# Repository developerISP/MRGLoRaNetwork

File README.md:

# Col Margherita LoRa Project (ROSY: Remote Observatory SYstem)
This is the repository for the school-work project between the Istitute of Polar Science ISP-CNR of Venice and the ITIS Max Planck of Villorba (TV)

# Who
The wonderful people involved in the ROSY project are all students, as they will never stop to learn! 

The young team in electronics, computer science, power management and telecommunications that built up the work is:
Nicolò Baseggio,
Davide Dal Bo,
Andrea De Marchi,
Michele Ferrarese,
Massimiliano Granziol,
Marco Martini,
Silvia Mondin,
Federico Peruzzo,
Roberto Pomiato,
Nicolò Rasera,
Nicola Voltarel

The group is trained and motivated by selfless and great teachers:
Alessandro Rocco Monteduro,
Monica Disarò,
Eugenio Rossi,
Giorgio Damian

The project is coordinated by enthusiastic researchers:
Federico Dallo,
Daniele Zannoni,
Fabrizio De Blasi,
Jacopo Gabrieli,
Carlo Barbante

# When
The project started in January 2020, continued throughout the tough Covid-19 pandemic thanks to the great motivation of the students and is on its way to be completed during the spring 2021. We were able to continue the development of hardware and software thanks to the distance learing (DAD) and tele-work. We have met at the ITIS Max Planck laboratories to build up the instrumentations and to perform several test, such as measuring the power comsumption and telecommunication capabilieties of the instruments. We were hosted at the Ca' Foscari University Campus in Via Torino and at the National Research Council (CNR) Col Margherita Observatory in the Belluno province.

# How

# Why

# Network
Files related to the acquisition, communication and ... are organized in the "network" directory. 

# Meteorology
Files for the analysis of meteorological variables are organized in the "meteorology" directory.
```
.
└── meteorology
    ├── data
    │   ├── MRG_2017_2018.csv
    │   └── P_Valles_2010_2020.csv
    ├── main.R
    └── outputs
        ├── MRGatmosphericpressuretypicalyear.csv
        ├── MRGatmosphericpressuretypicalyear.png
        ├── MRGrelativehumiditytypicalyear.csv
        ├── MRGrelativehumiditytypicalyear.png
        ├── MRGsolarradiationtypicalyear.csv
        ├── MRGsolarradiationtypicalyear.png
        ├── MRGtemperaturetypicalyear.csv
        ├── MRGtemperaturetypicalyear.png
        ├── MRGwinddirectiontypicalyear_autunno.png
        ├── MRGwinddirectiontypicalyear.csv
        ├── MRGwinddirectiontypicalyear_estate.png
        ├── MRGwinddirectiontypicalyear_inverno.png
        ├── MRGwinddirectiontypicalyear_primavera.png
        ├── MRGwindspeedtypicalyear.csv
        └── MRGwindspeedtypicalyear.png

3 directories, 18 files
```

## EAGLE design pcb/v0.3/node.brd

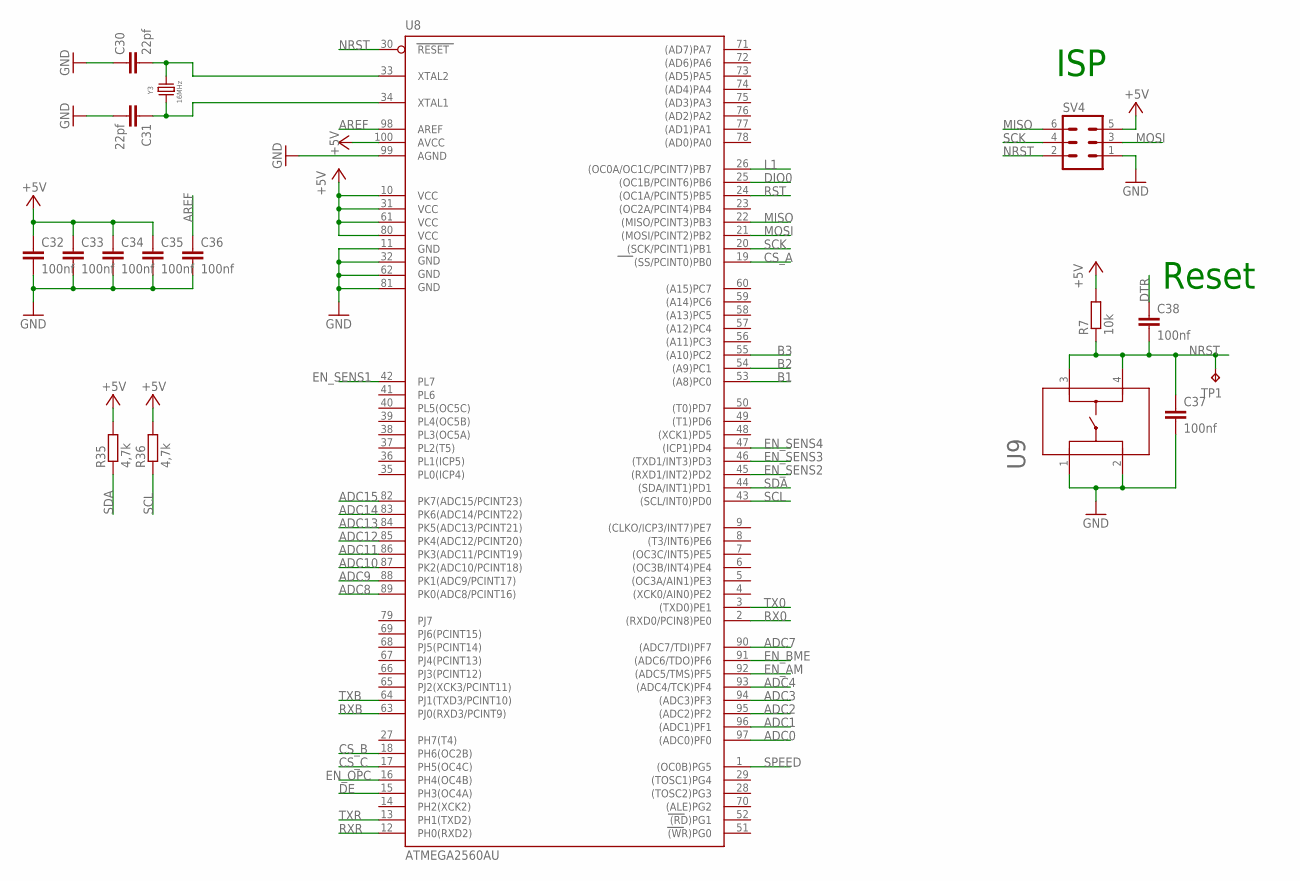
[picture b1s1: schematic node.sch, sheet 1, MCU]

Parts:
C30, C31: 22pf; C0603
C32, C33, C34, C35, C36, C37, C38: 100nf; C0805
R7: 10k; R0805
R35, R36: 4,7k; R0603
SV4: MA03-2
TP1: TPTP13R; TP13R
U8: ATMEGA2560AU; TQFP100
U9: 1-1825910-0; SWITCH_1-1825910-0
Y3: 16MHz; WE-XTAL_HC49/4H

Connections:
+5V: C32.1, C33.1, C34.1, C35.1, R7.2, R35.2, R36.2, SV4.5, U8.10 (VCC), U8.31 (VCC1), U8.61 (VCC2), U8.80 (VCC3), U8.100 (AVCC); also elsewhere on the board
ADC0: U8.97 ((ADC0)PF0)
ADC1: U8.96 ((ADC1)PF1); also elsewhere on the board
ADC2: U8.95 ((ADC2)PF2); also elsewhere on the board
ADC3: U8.94 ((ADC3)PF3); also elsewhere on the board
ADC4: U8.93 ((ADC4/TCK)PF4); also elsewhere on the board
ADC7: U8.90 ((ADC7/TDI)PF7); also elsewhere on the board
ADC8: U8.89 (PK0(ADC8/PCINT16))
ADC9: U8.88 (PK1(ADC9/PCINT17))
ADC10: U8.87 (PK2(ADC10/PCINT18))
ADC11: U8.86 (PK3(ADC11/PCINT19))
ADC12: U8.85 (PK4(ADC12/PCINT20))
ADC13: U8.84 (PK5(ADC13/PCINT21))
ADC14: U8.83 (PK6(ADC14/PCINT22))
ADC15: U8.82 (PK7(ADC15/PCINT23))
AREF: C36.1, U8.98 (AREF)
B1: U8.53 ((A8)PC0); also elsewhere on the board
B2: U8.54 ((A9)PC1); also elsewhere on the board
B3: U8.55 ((A10)PC2)
CS_A: U8.19 ((SS/PCINT0)PB0); also elsewhere on the board
CS_B: U8.18 (PH6(OC2B)); also elsewhere on the board
CS_C: U8.17 (PH5(OC4C)); also elsewhere on the board
DE: U8.15 (PH3(OC4A)); also elsewhere on the board
DIO0: U8.25 ((OC1B/PCINT6)PB6); also elsewhere on the board
DTR: C38.1; also elsewhere on the board
EN_AM: U8.92 ((ADC5/TMS)PF5); also elsewhere on the board
EN_BME: U8.91 ((ADC6/TDO)PF6); also elsewhere on the board
EN_OPC: U8.16 (PH4(OC4B)); also elsewhere on the board
EN_SENS1: U8.42 (PL7); also elsewhere on the board
EN_SENS2: U8.45 ((RXD1/INT2)PD2); also elsewhere on the board
EN_SENS3: U8.46 ((TXD1/INT3)PD3); also elsewhere on the board
EN_SENS4: U8.47 ((ICP1)PD4); also elsewhere on the board
GND: C30.1, C31.2, C32.2, C33.2, C34.2, C35.2, C36.2, C37.2, SV4.1, U8.11 (GND), U8.32 (GND1), U8.62 (GND2), U8.81 (GND3), U8.99 (AGND), U9.1, U9.2; also elsewhere on the board
L1: U8.26 ((OC0A/OC1C/PCINT7)PB7); also elsewhere on the board
MISO: SV4.6, U8.22 ((MISO/PCINT3)PB3); also elsewhere on the board
MOSI: SV4.3, U8.21 ((MOSI/PCINT2)PB2); also elsewhere on the board
unnamed: C30.2, U8.33 (XTAL2), Y3.2
unnamed: C31.1, U8.34 (XTAL1), Y3.1
NRST: C37.1, C38.2, R7.1, SV4.2, TP1.TP, U8.30 (RESET), U9.3, U9.4
RST: U8.24 ((OC1A/PCINT5)PB5); also elsewhere on the board
RX0: U8.2 ((RXD0/PCIN8)PE0); also elsewhere on the board
RXB: U8.63 (PJ0(RXD3/PCINT9)); also elsewhere on the board
RXR: U8.12 (PH0(RXD2)); also elsewhere on the board
SCK: SV4.4, U8.20 ((SCK/PCINT1)PB1); also elsewhere on the board
SCL: R36.1, U8.43 ((SCL/INT0)PD0); also elsewhere on the board
SDA: R35.1, U8.44 ((SDA/INT1)PD1); also elsewhere on the board
SPEED: U8.1 ((OC0B)PG5); also elsewhere on the board
TX0: U8.3 ((TXD0)PE1); also elsewhere on the board
TXB: U8.64 (PJ1(TXD3/PCINT10)); also elsewhere on the board
TXR: U8.13 (PH1(TXD2)); also elsewhere on the board

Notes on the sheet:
Reset
ISP

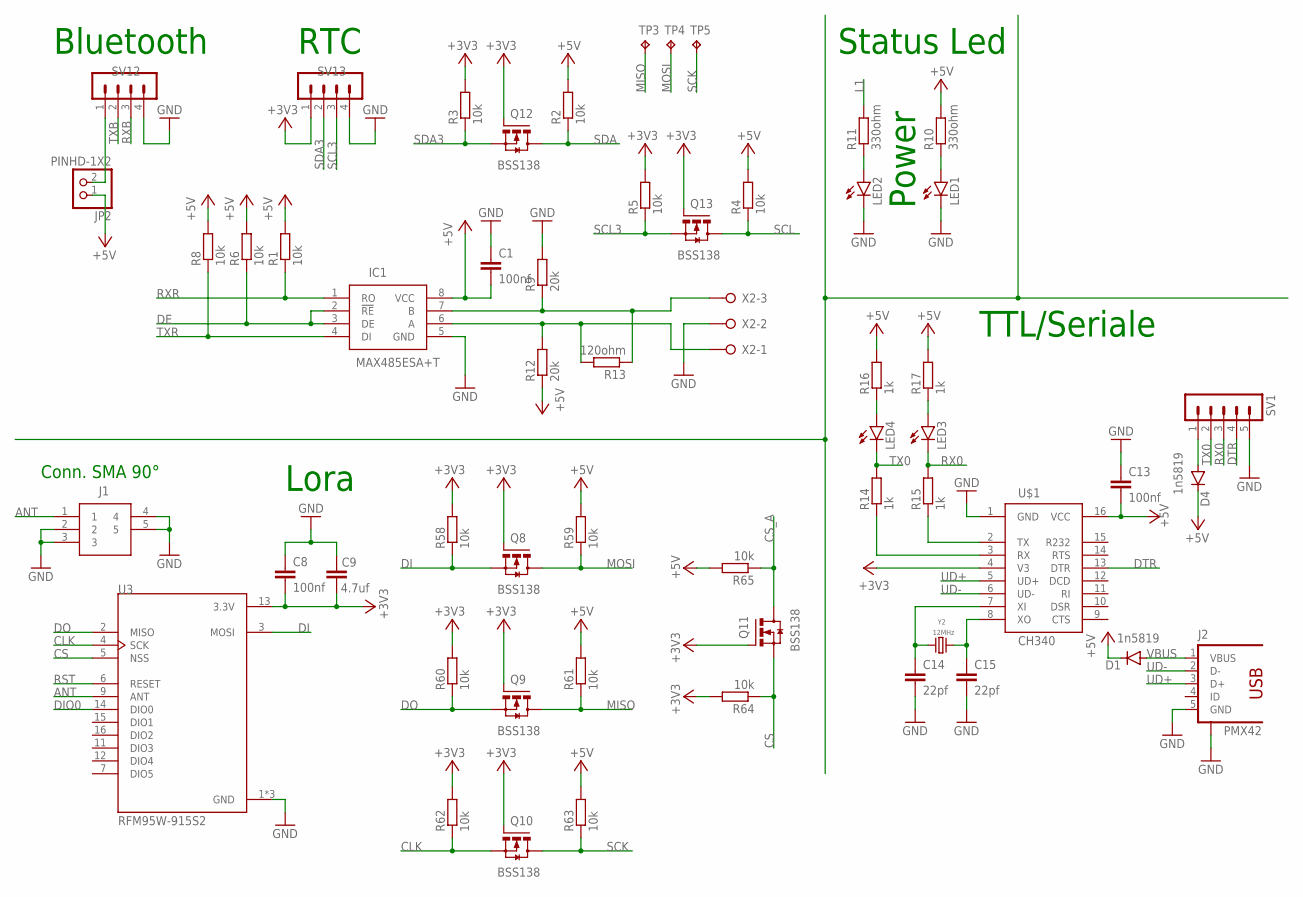
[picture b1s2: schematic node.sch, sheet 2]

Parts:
C1, C8, C13: 100nf; C0805
C9: 4.7uf; C1206K
C14, C15: 22pf; C0603
D1, D4: 1n5819; SOD123
IC1: MAX485ESA+T; SOIC127P600X175-8N
J1: 5-1814400-1; 518144001
J2: PMX42; PMX42_56579-0576
JP2: PINHD-1X2; 1X02
LED1, LED2, LED3, LED4: LEDSML0805; SML0805
Q8, Q9, Q10, Q11, Q12, Q13: BSS138; SOT23-3
R1, R2, R3, R4, R5, R6, R8, R58, R59, R60, R61, R62, R63, R64, R65: 10k; R0805
R9, R12: 20k; R0805
R10, R11: 330ohm; R0805
R13: 120ohm; R0805
R14, R15, R16, R17: 1k; R0805
SV1: MA05-1
SV12, SV13: MA04-1
TP3, TP4, TP5: TPTP13R; TP13R
U3: RFM95W-915S2; XCVR_RFM95W-915S2
U$1: CH340; SOIC16
X2: W237-3E
Y2: 12MHz; WE-XTAL_HC49/4H

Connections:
+3V3: C8.2, C9.1, Q8.1 (G), Q9.1 (G), Q10.1 (G), Q11.1 (G), Q12.1 (G), Q13.1 (G), R3.2, R5.2, R58.2, R60.2, R62.2, R64.2, SV13.1, U3.13 (3.3V), U$1.4 (V3); also elsewhere on the board
+5V: C1.2, C13.2, D1.C, D4.C, IC1.8 (VCC), JP2.1, R1.2, R2.2, R4.2, R6.2, R8.2, R10.2, R12.1, R16.2, R17.2, R59.2, R61.2, R63.2, R65.2, U$1.16 (VCC); also elsewhere on the board
ANT: J1.1, U3.9 (ANT)
CLK: Q10.2 (S), R62.1, U3.4 (SCK)
CS: Q11.2 (S), R64.1, U3.5 (NSS)
CS_A: Q11.3 (D), R65.1; also elsewhere on the board
DE: IC1.2 (!RE), IC1.3 (DE), R6.1; also elsewhere on the board
DI: Q8.2 (S), R58.1, U3.3 (MOSI)
DIO0: U3.14 (DIO0); also elsewhere on the board
DO: Q9.2 (S), R60.1, U3.2 (MISO)
DTR: SV1.4, U$1.13 (DTR); also elsewhere on the board
GND: C1.1, C8.1, C9.2, C13.1, C14.2, C15.2, IC1.5 (GND), J1.2, J1.3, J1.4, J1.5, J2.5 (GND), J2.S1 (S), J2.S2 (S), J2.S3 (S), J2.S4 (S), LED1.C, LED2.C, R9.2, SV1.5, SV12.4, SV13.4, U3.1 (GND), U3.8 (GND), U3.10 (GND), U$1.1 (GND), X2.2; also elsewhere on the board
L1: R11.2; also elsewhere on the board
MISO: Q9.3 (D), R61.1, TP3.TP; also elsewhere on the board
MOSI: Q8.3 (D), R59.1, TP4.TP; also elsewhere on the board
unnamed: JP2.2, SV12.1
unnamed: LED1.A, R10.1
unnamed: LED2.A, R11.1
unnamed: R15.1, U$1.2 (TX)
unnamed: R14.1, U$1.3 (RX)
unnamed: C15.1, U$1.8 (XO), Y2.1
unnamed: C14.1, U$1.7 (XI), Y2.2
unnamed: LED3.A, R17.1
unnamed: LED4.A, R16.1
unnamed: D4.A, SV1.1
unnamed: IC1.6 (A), R12.2, R13.2, X2.1
unnamed: IC1.7 (B), R9.1, R13.1, X2.3
RST: U3.6 (RESET); also elsewhere on the board
RX0: LED3.C, R15.2, SV1.3; also elsewhere on the board
RXB: SV12.3; also elsewhere on the board
RXR: IC1.1 (RO), R1.1; also elsewhere on the board
SCK: Q10.3 (D), R63.1, TP5.TP; also elsewhere on the board
SCL: Q13.3 (D), R4.1; also elsewhere on the board
SCL3: Q13.2 (S), R5.1, SV13.3
SDA: Q12.3 (D), R2.1; also elsewhere on the board
SDA3: Q12.2 (S), R3.1, SV13.2
TX0: LED4.C, R14.2, SV1.2; also elsewhere on the board
TXB: SV12.2; also elsewhere on the board
TXR: IC1.4 (DI), R8.1; also elsewhere on the board
UD+: J2.3 (D+), U$1.5 (UD+)
UD-: J2.2 (D-), U$1.6 (UD-)
VBUS: D1.A, J2.1 (VBUS)

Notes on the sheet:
Power
Lora
Conn. SMA 90°
TTL/Seriale
Status Led
Bluetooth
RTC

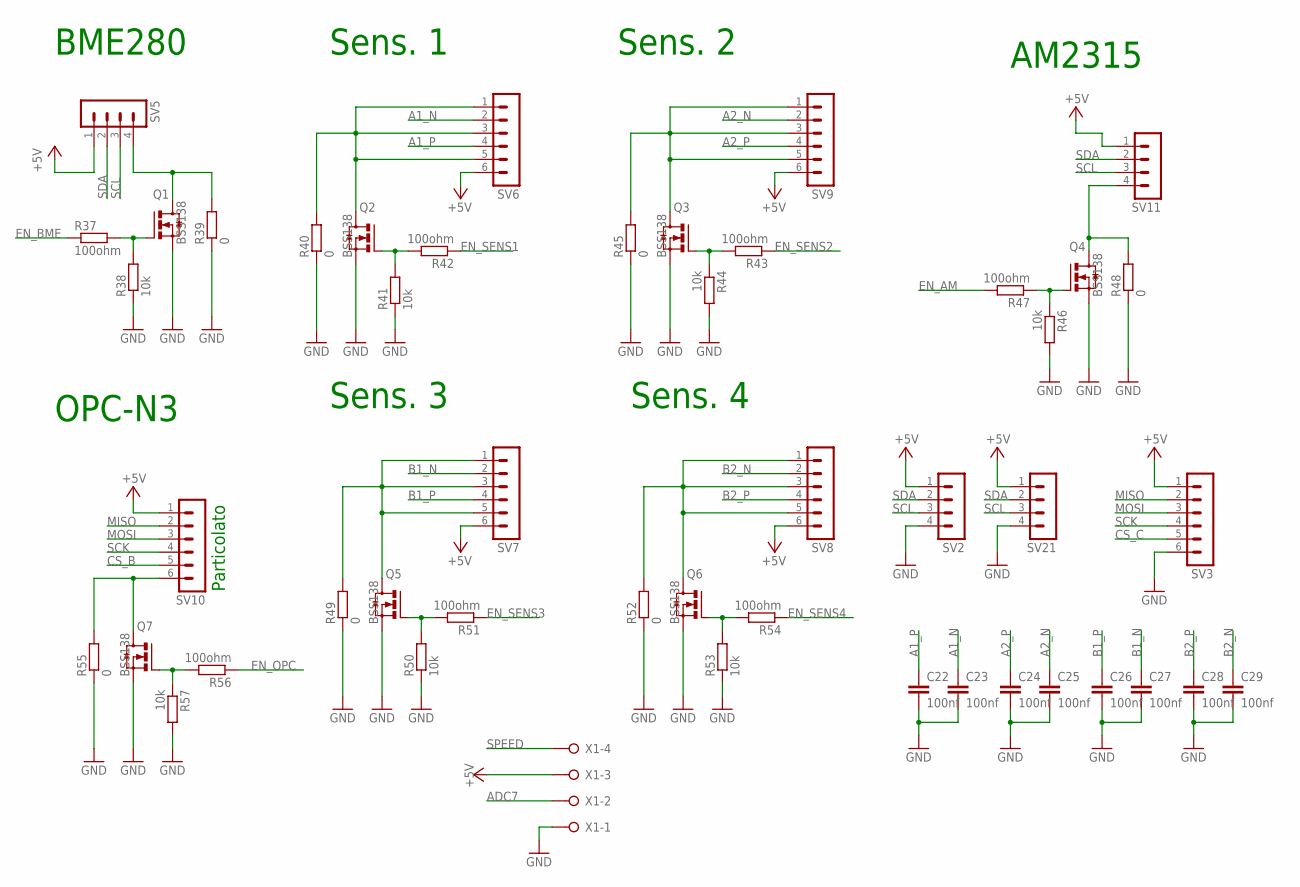
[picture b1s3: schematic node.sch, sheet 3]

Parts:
C22, C23, C24, C25, C26, C27, C28, C29: 100nf; C0805
Q1, Q2, Q3, Q4, Q5, Q6, Q7: BSS138; SOT23-3
R37, R42, R43, R47, R51, R54, R56: 100ohm; R0805W
R38, R41, R44, R46, R50, R53, R57: 10k; R0805W
R39, R40, R45, R48, R49, R52, R55: 0; R0603
SV2, SV5, SV11, SV21: MA04-1
SV3, SV6, SV7, SV8, SV9, SV10: MA06-1
X1: W237-04P; W237-4P

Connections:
+5V: SV2.1, SV3.1, SV5.1, SV6.6, SV7.6, SV8.6, SV9.6, SV10.1, SV11.1, SV21.1, X1.3; also elsewhere on the board
A1_N: C23.1, SV6.2; also elsewhere on the board
A1_P: C22.1, SV6.4; also elsewhere on the board
A2_N: C25.1, SV9.2; also elsewhere on the board
A2_P: C24.1, SV9.4; also elsewhere on the board
ADC7: X1.2; also elsewhere on the board
B1_N: C27.1, SV7.2; also elsewhere on the board
B1_P: C26.1, SV7.4; also elsewhere on the board
B2_N: C29.1, SV8.2; also elsewhere on the board
B2_P: C28.1, SV8.4; also elsewhere on the board
CS_B: SV10.5; also elsewhere on the board
CS_C: SV3.5; also elsewhere on the board
EN_AM: R47.2; also elsewhere on the board
EN_BME: R37.1; also elsewhere on the board
EN_OPC: R56.1; also elsewhere on the board
EN_SENS1: R42.1; also elsewhere on the board
EN_SENS2: R43.1; also elsewhere on the board
EN_SENS3: R51.1; also elsewhere on the board
EN_SENS4: R54.1; also elsewhere on the board
GND: C22.2, C23.2, C24.2, C25.2, C26.2, C27.2, C28.2, C29.2, Q1.2 (S), Q2.2 (S), Q3.2 (S), Q4.2 (S), Q5.2 (S), Q6.2 (S), Q7.2 (S), R38.1, R39.1, R40.1, R41.1, R44.2, R45.1, R46.2, R48.1, R49.1, R50.1, R52.1, R53.1, R55.1, R57.2, SV2.4, SV3.6, SV21.4, X1.1; also elsewhere on the board
MISO: SV3.2, SV10.2; also elsewhere on the board
MOSI: SV3.3, SV10.3; also elsewhere on the board
unnamed: Q1.3 (D), R39.2, SV5.4
unnamed: Q1.1 (G), R37.2, R38.2
unnamed: Q6.3 (D), R52.2, SV8.1, SV8.3, SV8.5
unnamed: Q2.3 (D), R40.2, SV6.1, SV6.3, SV6.5
unnamed: Q5.3 (D), R49.2, SV7.1, SV7.3, SV7.5
unnamed: Q2.1 (G), R41.2, R42.2
unnamed: Q4.3 (D), R48.2, SV11.4
unnamed: Q3.3 (D), R45.2, SV9.1, SV9.3, SV9.5
unnamed: Q3.1 (G), R43.2, R44.1
unnamed: Q4.1 (G), R46.1, R47.1
unnamed: Q6.1 (G), R53.2, R54.2
unnamed: Q5.1 (G), R50.2, R51.2
unnamed: Q7.3 (D), R55.2, SV10.6
unnamed: Q7.1 (G), R56.2, R57.1
SCK: SV3.4, SV10.4; also elsewhere on the board
SCL: SV2.3, SV5.3, SV11.3, SV21.3; also elsewhere on the board
SDA: SV2.2, SV5.2, SV11.2, SV21.2; also elsewhere on the board
SPEED: X1.4; also elsewhere on the board

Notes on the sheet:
OPC-N3
AM2315
Particolato
Sens. 1
Sens. 2
Sens. 3
Sens. 4
BME280

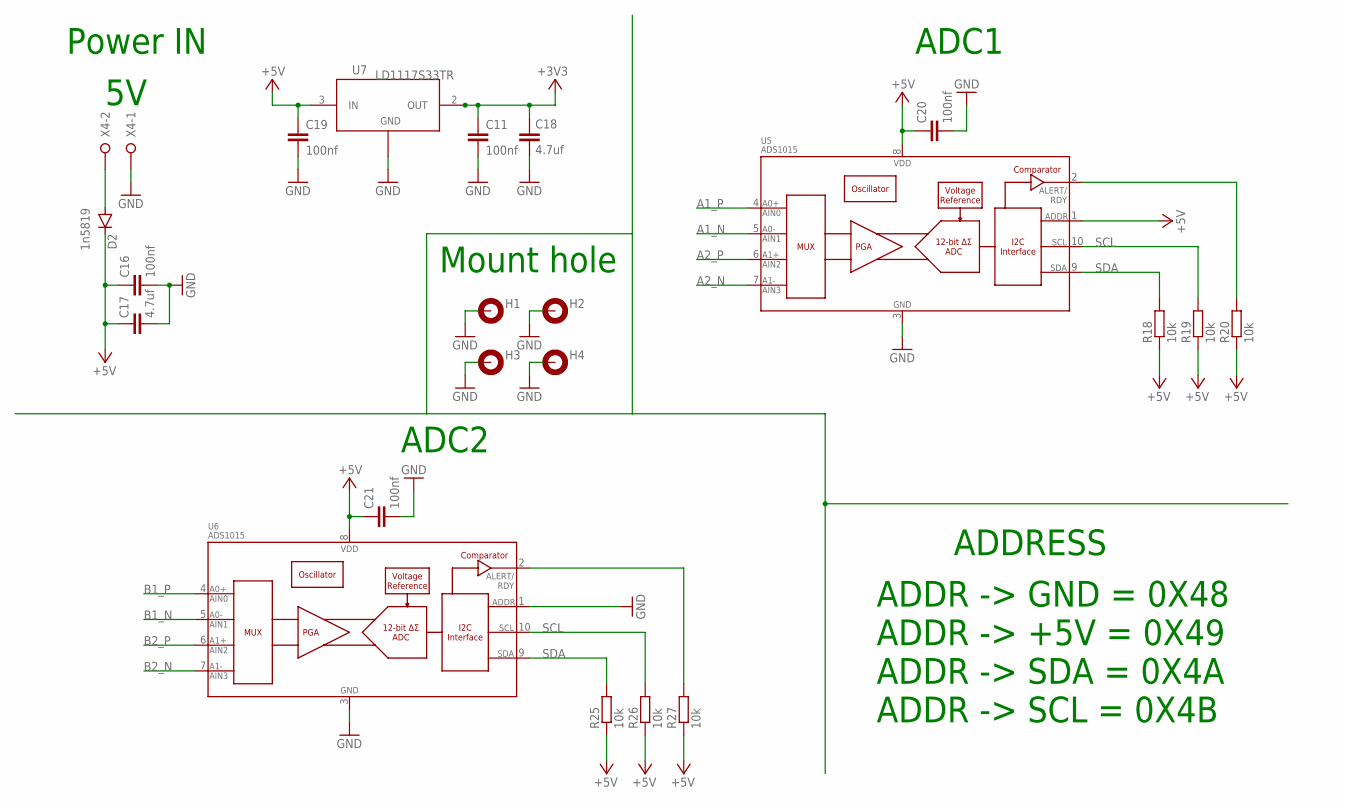
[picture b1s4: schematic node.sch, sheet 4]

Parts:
C11, C16, C19, C20, C21: 100nf; C0805
C17, C18: 4.7uf; C1206K
D2: 1n5819; SOD123
H1, H2, H3, H4: MOUNT-PAD-ROUND3.2; 3,2-PAD
R18, R19, R20, R25, R26, R27: 10k; R0805
U5, U6: ADS1015; MSOP10
U7: LD1117S33TR; SOT-223
X4: W237-02P; W237-132

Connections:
+3V3: C11.1, C18.1, U7.2 (OUT), U7.4; also elsewhere on the board
+5V: C16.1, C17.1, C19.1, C20.1, C21.1, D2.C, R18.1, R19.1, R20.1, R25.1, R26.1, R27.1, U5.1 (ADDR), U5.8 (VDD), U6.8 (VDD), U7.3 (IN); also elsewhere on the board
A1_N: U5.5 (AIN1); also elsewhere on the board
A1_P: U5.4 (AIN0); also elsewhere on the board
A2_N: U5.7 (AIN3); also elsewhere on the board
A2_P: U5.6 (AIN2); also elsewhere on the board
B1_N: U6.5 (AIN1); also elsewhere on the board
B1_P: U6.4 (AIN0); also elsewhere on the board
B2_N: U6.7 (AIN3); also elsewhere on the board
B2_P: U6.6 (AIN2); also elsewhere on the board
GND: C11.2, C16.2, C17.2, C18.2, C19.2, C20.2, C21.2, H1.B3,2, H2.B3,2, H3.B3,2, H4.B3,2, U5.3 (VSS), U6.1 (ADDR), U6.3 (VSS), U7.1 (ADJ/GND), X4.1; also elsewhere on the board
unnamed: D2.A, X4.2
unnamed: R20.2, U5.2 (ALERT/RDY)
unnamed: R27.2, U6.2 (ALERT/RDY)
SCL: R19.2, R26.2, U5.10 (SCL), U6.10 (SCL); also elsewhere on the board
SDA: R18.2, R25.2, U5.9 (SDA), U6.9 (SDA); also elsewhere on the board

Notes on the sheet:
ADC2
ADC1
ADDRESS
ADDR -> +5V = 0X49
ADDR -> GND = 0X48
ADDR -> SDA = 0X4A
ADDR -> SCL = 0X4B
Power IN
Mount hole

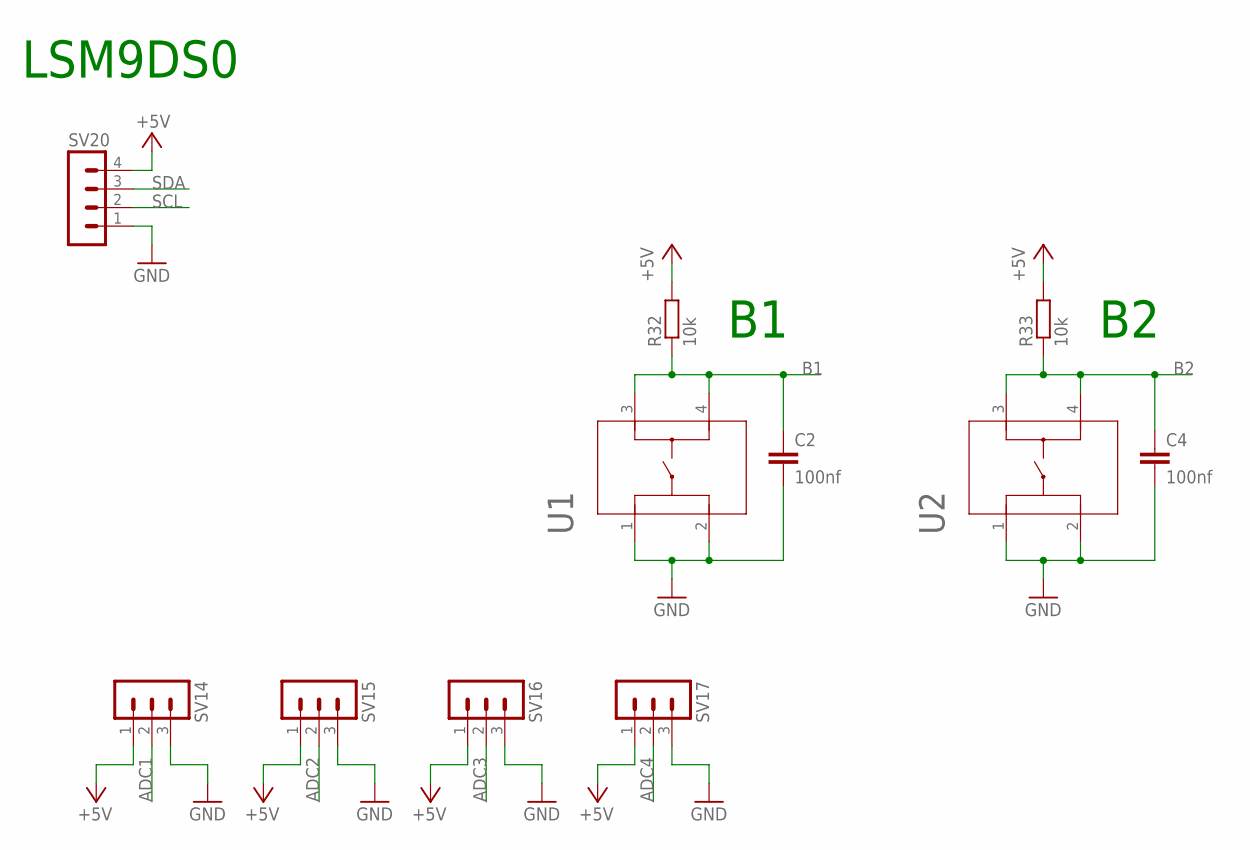
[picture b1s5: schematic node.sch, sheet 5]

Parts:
C2, C4: 100nf; C0805
R32, R33: 10k; R0805
SV14, SV15, SV16, SV17: MA03-1
SV20: MA04-1
U1, U2: 1-1825910-0; SWITCH_1-1825910-0

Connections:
+5V: R32.2, R33.2, SV14.1, SV15.1, SV16.1, SV17.1, SV20.4; also elsewhere on the board
ADC1: SV14.2; also elsewhere on the board
ADC2: SV15.2; also elsewhere on the board
ADC3: SV16.2; also elsewhere on the board
ADC4: SV17.2; also elsewhere on the board
B1: C2.1, R32.1, U1.3, U1.4; also elsewhere on the board
B2: C4.1, R33.1, U2.3, U2.4; also elsewhere on the board
GND: C2.2, C4.2, SV14.3, SV15.3, SV16.3, SV17.3, SV20.1, U1.1, U1.2, U2.1, U2.2; also elsewhere on the board
SCL: SV20.2; also elsewhere on the board
SDA: SV20.3; also elsewhere on the board

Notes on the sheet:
LSM9DS0

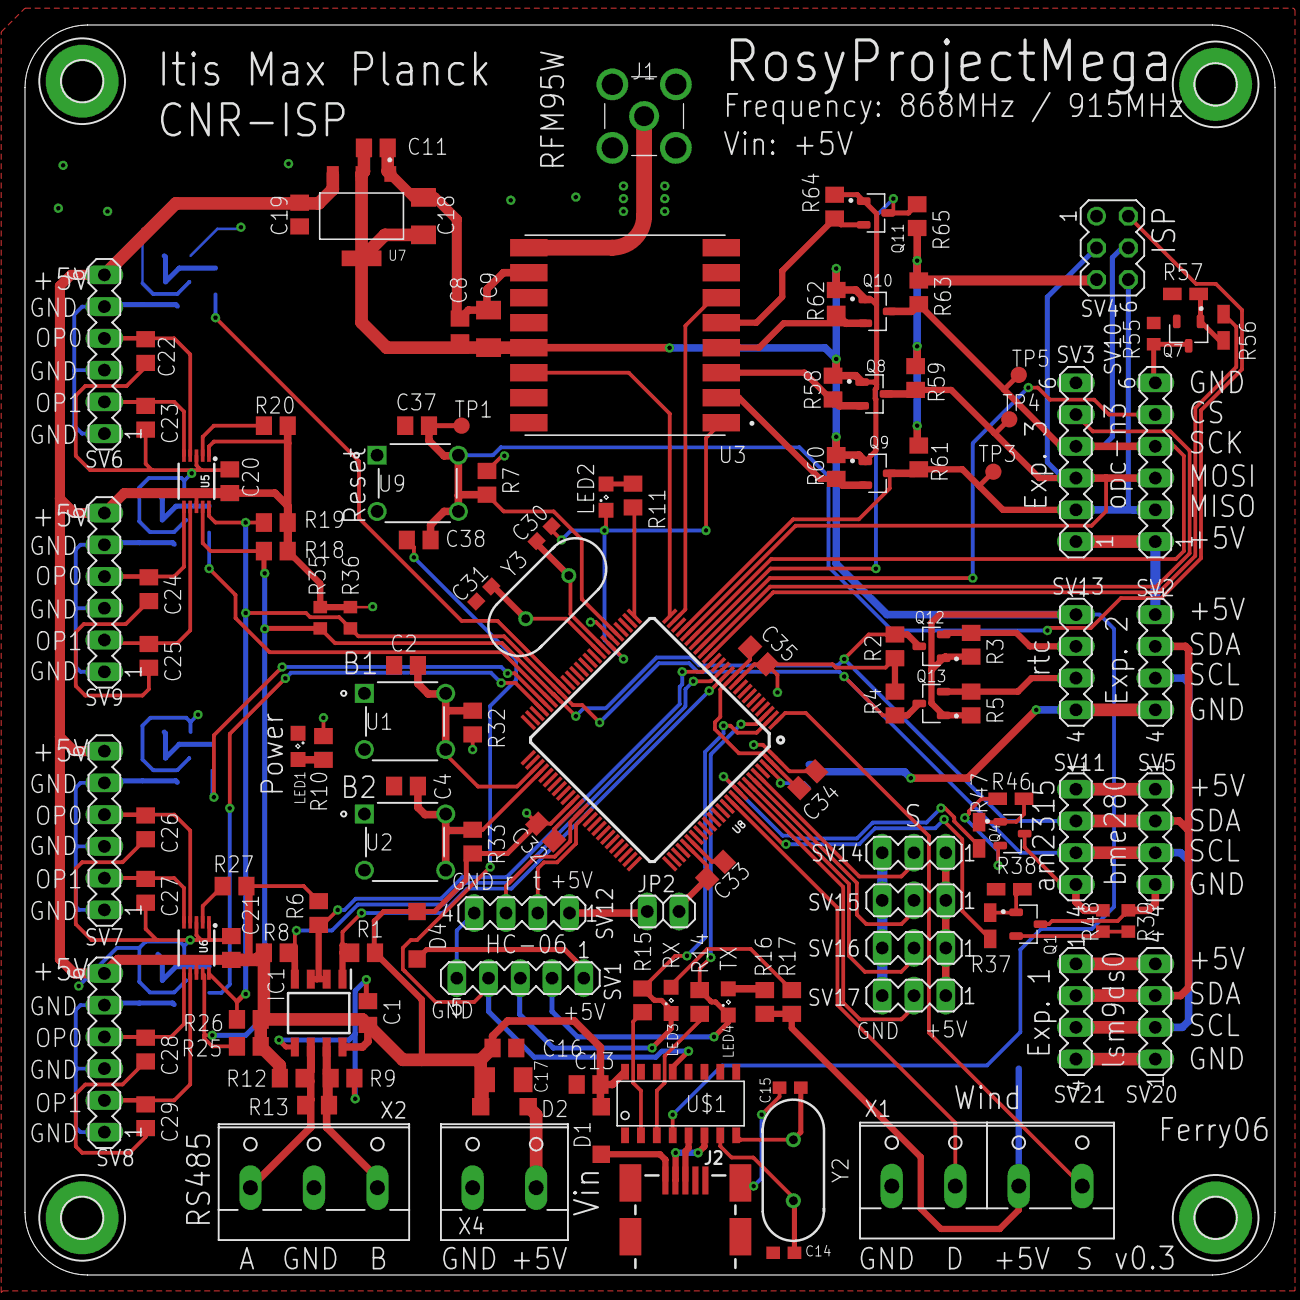
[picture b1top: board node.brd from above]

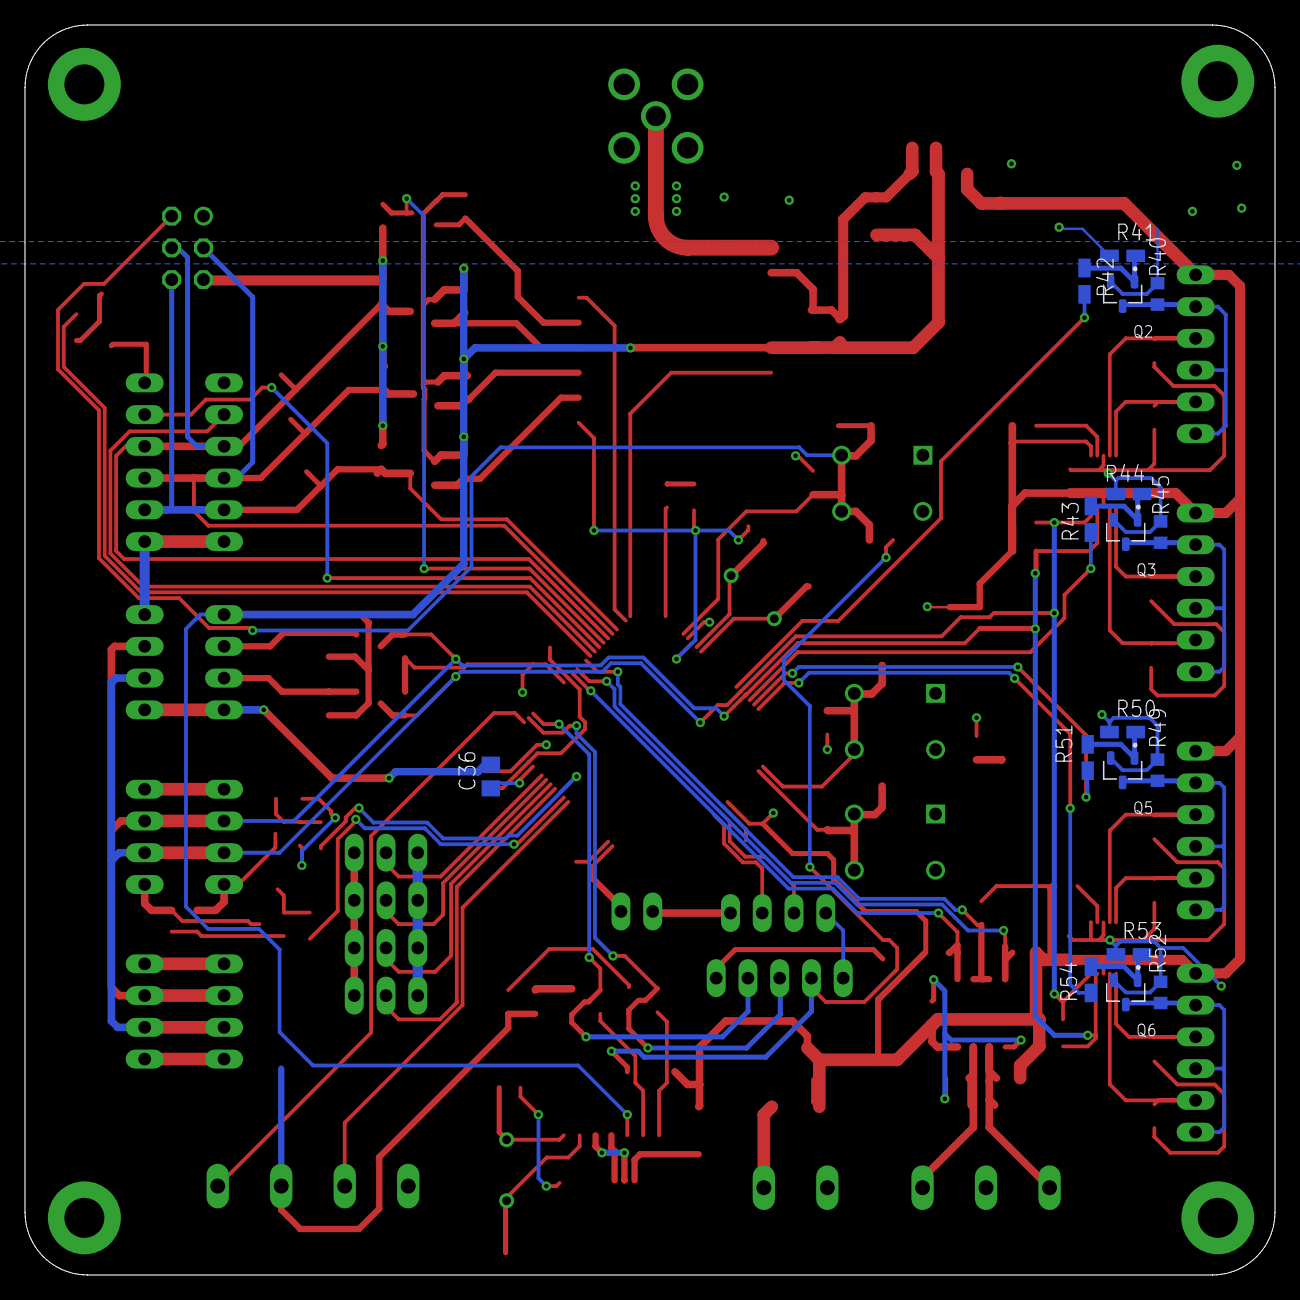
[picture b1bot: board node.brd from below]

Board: 2 copper layers, 100.0 x 100.0 mm, 153 parts (17 on the bottom side), 88 nets.

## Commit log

2020-04-01 Add files via upload
    main R script for the analysis of Temperature data
2020-04-01 Rename lora_driver.c to network/lora_driver.c
    changing directory of file
2020-04-01 Rename main.c to network/main.c
    changing directory of file
2020-04-01 Add files via upload
    lavoro sulle variabili meteo quasi completo. manca la direzione del vento
2020-04-01 Add files via upload
    update main
2020-06-06 v 1.0.1
2020-06-19 1.0.2
    tutte le informazioni sulle modifiche sono state scritte nel README
2020-06-27 Create sd
2020-07-25 Create Versione 5
2020-07-25 Create Versione 3
2020-10-10 Create msg.txt
    Questo è il file contenente il "messaggio tipo" di un nodo. La descrizione del file, da Baseggio e Granziol, è la seguente:
    Ogni pacchetto comunicato in seriale dal gateway al raspberry cominica con "sp"
    e terminata con "ep". Dopo "sp" è presente un header composto da, in ordine di
    successione, l'indirizzo dell'endnode che ha inviato il pacchetto, il numero di
    letture, il voltaggio della battiera, la corrente della batteria, il S/N di
    LoRa e RSSI di LoRa. Finito l'header ci sono le letture, in numero indicato
2020-10-10 Create sendmsg.sh
    Questo programma serve per mandare il messaggio "msg.txt" attraverso la porta seriale di una macchina linux (ubuntu). La macchina con cui sono stati fatti i test è un ubuntu 18.04 con un adattatore s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
2020-10-10 Create serial_read.py
    Questo programma, eseguito su raspberry pi (nei test RP3b+) legge continuamente dalla porta seriale e stampa su terminale il messaggio in arrivo. Questo programma è utile per verificare il funzioname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
2020-10-10 Create serial_save_base.py
    Questo programma serve salvare il messaggio in arrivo sulla porta seriale su file "dataFile.txt"
2020-10-10 Create serial_parse_gateway.py
    Versione in evoluzione del programma da eseguire sul raspberry pi collegato in seriale al gateway. Lo scopo del programma è leggere e bufferizzare il messaggio seriale inviato dal gateway. Successiva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
2020-10-10 Create 20201010MrgRosyGatewayAll.txt
    Esempio di file di dati giornaliero.
2021-03-13 add py dependencies
2021-03-13 add py gitignore
2021-03-13 add backend
2021-03-29 Update README.md
    Aggiunta descrizione al file readme
2021-05-04 Create endNode

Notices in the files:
parts and their libraries:
SparkFun-IC-Conversion: Licensing: Creative Commons ShareAlike 4.0 International - https://creativecommons.org/licenses/by-sa/4.0
Wurth_Quartz Crystals: Copyright: Würth Elektronik
COPYRIGHT: Copyright (C) 2016 Accelerated Designs. All rights reserved
